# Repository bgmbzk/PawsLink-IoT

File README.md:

# 🐾 PawsLink IoT: The Elite Cat Gate Controller

Selam! Bu proje, evin asıl sahibi olan kedimin balkon kapısında mahsur kalma krizlerine (ve benim her seferinde bir "kapı görevlisi" edasıyla yerimden kalkmama) son vermek için geliştirildi. Başta küçük bir can sıkıntısı gibi görünse de, süreç içinde evrim geçirerek tam kapsamlı bir **Embedded System & IoT** projesine dönüştü.

## 📸 Tasarım Süreci ve Görseller

### 🎨 Şematik Tasarım
Projenin elektriksel bağlantıları ve ESP32 entegrasyonu:

---

### 🛣️ PCB Layout
Hassas sinyal yolları ve RF performansını korumak için tasarlanan Anten Keep-out bölgesi:

---

### 🧊 3D Modelleme
Üretim sonrası kartın fiziksel görünümü ve komponent yerleşimi:

## 🐱 Neden PawsLink?
Kedim, balkona çıkmak istediğinde kapının önünde kendine has bir frekansta seslenerek beni göreve çağırıyor. **PawsLink**, bu işitsel sinyalleri (miyavlamaları) algılayıp mekanik bir kolu tetikleyen, böylece kedime kendi özgürlüğünü sunan akıllı bir sistemdir.

## 🛠 Teknik Gelişim & Mühendislik Detayları
Proje başlangıçta **ATmega** tabanlıydı; ancak hem performansını artırmak hem de modern bağlantı özelliklerinden (Wi-Fi/Bluetooth) faydalanmak amacıyla mimariyi **ESP32**’ye taşıdım. Tasarımda dikkat ettiğim bazı kritik teknik noktalar:

* **RF Performansı (Anten Keep-out):** ESP32'nin üzerindeki PCB antenin verimli çalışması için, antenin altında kalan tüm katmanlarda bakır dökümü iptal edildi (No-copper zone).
* **Hassas PCB Layout:** USB-C güç girişi gibi yüksek yoğunluklu pinlerde kısa devre riskini önlemek için özel clearance (güvenlik mesafesi) ayarları yapıldı.
* **EMI ve Gürültü Yönetimi:** Güç hatları üzerine yerleştirilen decoupling kapasitörleri ile dijital gürültü minimize edildi, analog ses sensörünün daha kararlı çalışması sağlandı.
* **Hatasız Tasarım:** Endüstriyel standartlarda, **0 DRC Error** ve **0 Unconnected Items** ile üretime hazır hale getirildi.

 ---

# 🛠 Donanım Güncellemesi: V1.1 - Güç Optimizasyonu

Sistem kararlılığını ve motor performansını artırmak için yapılan iyileştirmeler:

* **Yol Kalınlaştırma (Power Tracks):** Motoru besleyen ana hatlar ve motor çıkış yolları **40 mil (~1.0 mm)** genişliğine çıkarıldı. Bu sayede motorun çektiği anlık akım, kartta ısınmaya veya voltaj düşümüne sebep olmadan güvenle iletilebiliyor.
* **Güç Otobanı:** Barrel Jack girişinden başlayarak Diyot, Kapasitörler ve Motor Sürücüye (DRV8833) giden hat "Güç Otobanı" mantığıyla optimize edildi. Bu güncelleme, motor zorlandığında bile ESP32'nin stabil çalışmasını (brown-out önleme) sağlar.
* **GND Plane:** Toprak hattı kesintisiz bakır döküm (GND Plane) olarak tasarlanarak hem parazitler engellendi hem de termal yönetim iyileştirildi.

---

## 📂 Dosya Yapısı
* `/Hardware`: KiCad şematik ve PCB layout dosyaları.
* `/Production`: Üretime hazır Gerber ve Drill dosyaları (PawsLink_Final_v1.zip).
* `/Firmware`: ESP32 için yazılmış IoT kontrol kodları.

---

### 🚀 Nasıl Çalışır?
1. PCB sipariş edilir ve bileşenler lehimlenir.
2. ESP32 yazılımı yüklenir.
3. Kedinin "miyav" frekansı kalibre edilir.
4. Koltuğa yaslanılır ve kedinin kendi kapısını açışı izlenir. ✨

---

## 🚀 Son Güncellemeler (Mayıs 2026)

Bu donanım revizyonu, güvenlik önlemlerine odaklanmakta ve sistemi akıllı yazılım entegrasyonuna hazırlamaktadır. Proje, kapı hareketi sırasında kedi güvenliğini sağlamak için proaktif önlemler içerecek şekilde geliştirilmiştir.

### Donanım v1.2 İyileştirmeleri
*   **Akıllı Engel Algılama**: HuskyLens entegrasyonu için özel bir 4-pinli konnektör (**J4**) eklendi. Bu sayede, mekanizma çalışmadan önce yapay zeka destekli algılama ile kedinin kapı eşiğinde olup olmadığı kontrol edilebilecektir.
*   **Görsel Durum LED'i**: Sistem durumunu ve olası engelleri gerçek zamanlı olarak bildirmek için yeni bir gösterge LED'i eklendi.
*   **Güç Kararlılığı**: ESP32 ve motor sürücüsünün yük altında kararlı çalışması için PCB yolları, net atamaları (USB-C pin eşleme düzeltmeleri dahil) ve bakır alanlar optimize edildi.
*   **Üretime Hazır Düzen**: Fiziksel PCB üretimine hazırlık amacıyla tasarım kuralı hataları (DRC) ve açıklık (clearance) ihlalleri giderildi.

### Güncel Proje Görselleri

#### Yeni Şematik Tasarımı

#### Yeni PCB Tasarımı

#### 3D Donanım Modeli

## 💻 Yazılım Özellikleri (Firmware)

Projenin yazılımı ESP32 üzerinde C++ (Arduino) kullanılarak geliştirilmiştir. Temel çalışma mantığı şu şekildedir:

* **Tetikleme:** LM358 amfi devresi üzerinden gelen analog ses verisiyle kedinin miyavlaması algılanır.
* **Güvenlik:** HuskyLens AI kamera, I2C üzerinden ESP32 ile haberleşerek kedinin kapı eşiğinde olup olmadığını denetler.
* **Akıllı Döngü:** Kapı sadece miyavlama duyulduğunda açılır ve kedi eşikten tamamen ayrıldığında (HuskyLens onayıyla) güvenli bir şekilde kapanır.
* **Enerji Tasarrufu:** DRV8833 motor sürücüsü, işlem yapılmadığı anlarda `SLEEP` moduna alınarak güç tüketimi minimize edilir.
---

*Not: Bu donanım versiyonu ile eşzamanlı geliştirilen ESP32 yazılımı güncellenmelere açıktır. *

**Not2:** Bu proje yapılırken hiçbir kedi mahsur bırakılmamıştır. Aksine, artık evin kapıları onun kontrolü altında! 🐈‍⬛🚀

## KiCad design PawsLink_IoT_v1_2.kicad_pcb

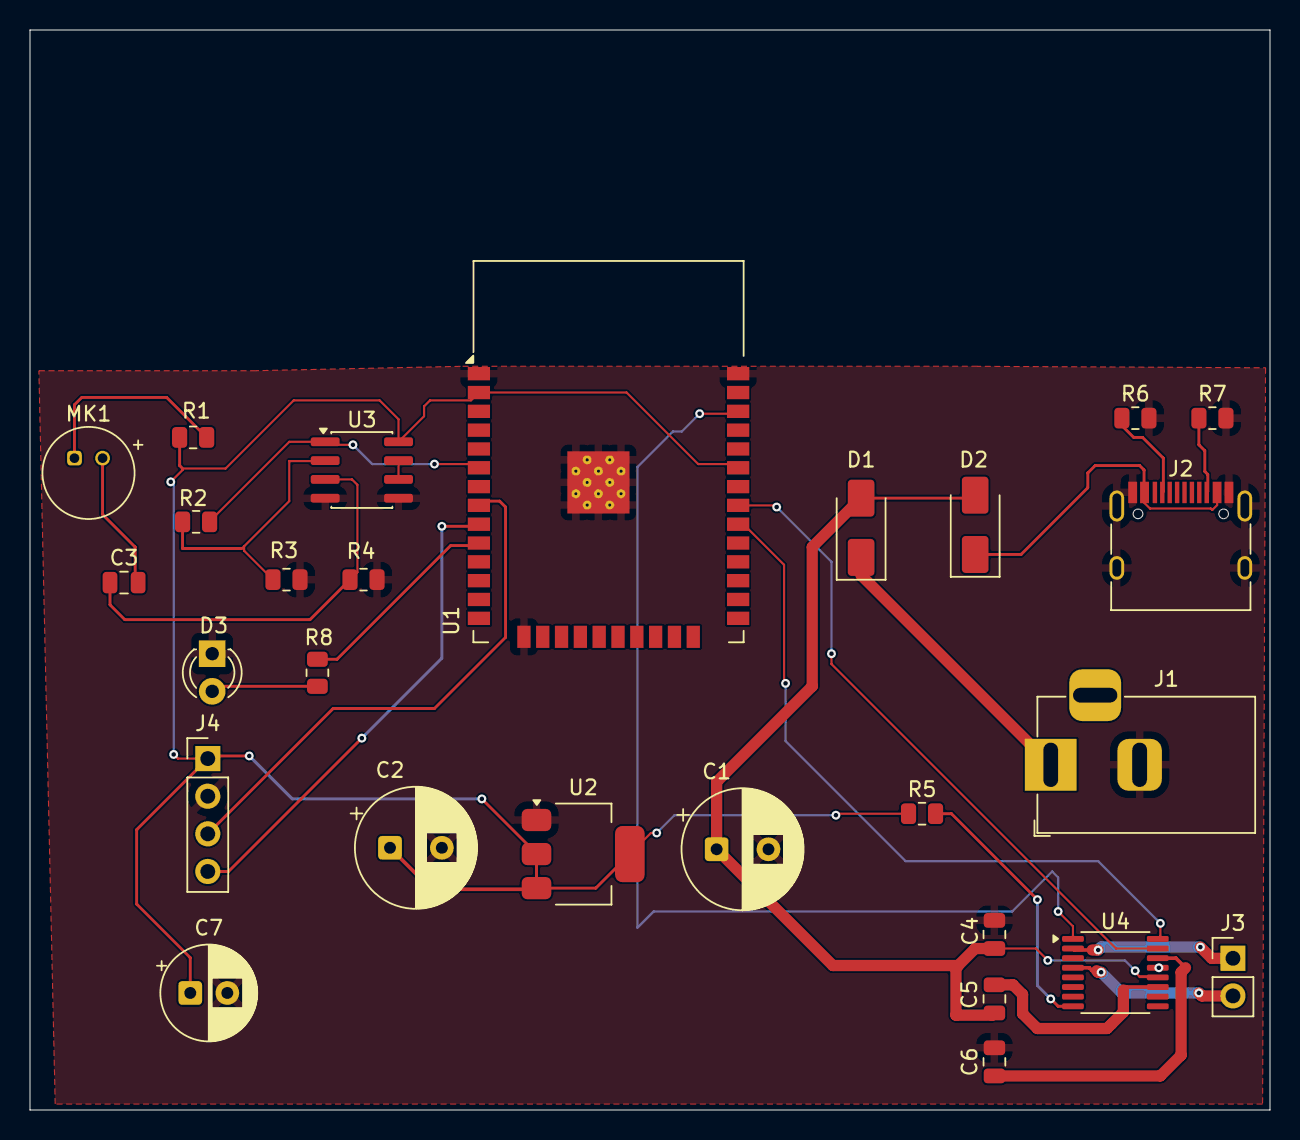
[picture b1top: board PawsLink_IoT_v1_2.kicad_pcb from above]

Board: 2 copper layers, 83.7 x 72.9 mm, 27 parts (0 on the bottom side), 25 nets.

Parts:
C1, C2: C_Polarized; CP_Radial_D8.0mm_P3.50mm
C3: 100nF; C_0805_2012Metric
C4: 100uF; C_0805_2012Metric
C5: 10nF; C_0805_2012Metric
C6: 2.2muF; C_0805_2012Metric
C7: 100uF; CP_Radial_D6.3mm_P2.50mm
D1, D2: SS34; D_SMA
D3: LED; LED_D3.0mm
J1: Barrel_Jack_MountingPin; BarrelJack_Horizontal
J2: USB_C_Receptacle_PowerOnly_6P; USB_C_Receptacle_HRO_TYPE-C-31-M-12
J3: Conn_01x02; PinHeader_1x02_P2.54mm_Vertical
J4: Conn_01x04; PinHeader_1x04_P2.54mm_Vertical
MK1: Microphone_Condenser; POM-2244P-C3310-2-R
R1: 2.2k; R_0805_2012Metric
R2: 100kΩ; R_0805_2012Metric
R3: 1kΩ; R_0805_2012Metric
R4: 1MΩ; R_0805_2012Metric
R5: 10kΩ; R_0805_2012Metric
R6, R7: 5.1kΩ; R_0805_2012Metric
R8: 220; R_0805_2012Metric
U1: ESP32-WROOM-32
U2: AMS1117CS-3.3; SOT-223-3_TabPin2
U3: LM358; SOIC-8_3.9x4.9mm_P1.27mm
U4: DRV8833PW; TSSOP-16_4.4x5mm_P0.65mm

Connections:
GND: C1.2, C2.2, C4.2, C6.2, C7.2, D3.1 (K), J1.2, J2.A1, J2.A12 (GND), J2.B1, J2.B12 (GND), J2.S1 (SHIELD), J4.2, R3.2, R4.2, R6.2, R7.2, U1.1 (GND), U1.15 (GND), U1.38 (GND), U1.39 (GND), U2.1 (GND), U3.4 (V-), U3.5 (+), U4.13 (GND)
unnamed: C1.1, C4.1, C5.2, D1.2 (A), D2.2 (A), U4.12 (VM)
unnamed: D1.1 (K), J1.1
unnamed: D2.1 (K), J2.A4, J2.A9 (VBUS), J2.B4, J2.B9 (VBUS)
unnamed: D3.2 (A), R8.2
unnamed: J2.A5 (CC1), R6.1
unnamed: J2.B5 (CC2), R7.1
unnamed: J3.1, U4.2 (AOUT1)
unnamed: J3.2, U4.4 (AOUT2)
unnamed: C2.1, C7.1, J4.1, R1.1, R5.1, U1.2 (VDD), U1.33 (IO21), U2.2 (VO), U2.3 (VO), U3.8 (V+)
unnamed: J4.3, U1.8 (IO32)
unnamed: J4.4, U1.9 (IO33)
unnamed: C3.2, MK1.2 (+)
unnamed: MK1.1 (-), R1.2
unnamed: U1.30 (IO18), U4.16 (AIN1)
unnamed: U1.31 (IO19), U4.15 (AIN2)
unnamed: U1.36 (IO22), U4.1 (~SLEEP)
unnamed: R8.1, U1.10 (IO25)
unnamed: R2.2, U1.6 (IO34), U3.1
unnamed: C3.1, R4.1, U3.3 (+)
unnamed: R2.1, R3.1, U3.2 (-)
unnamed: U3.6 (-), U3.7
unnamed: C5.1, U4.11 (VCP)
unnamed: C6.1, U4.14 (VINT)
unnamed: R5.2, U4.8 (~FAULT)

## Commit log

2026-04-29 Fix typo in README.md description
    Corrected a typo in the description of PawsLink.
2026-04-29 Add hardware update V1.1 for power optimization
    Refactor: Widen power traces to 40mils for increased current capacity and system stability
2026-05-06 v1.2 Update: STM32 Shift & PCB Design
    ESP32 Hardware Update: Refined the existing ESP32-based design for better stability and future firmware development.
    Safety Features: Added a dedicated LED and HuskyLens connector (J4) to detect if the cat is standing in the doorway, preventing accidental closure.
    PCB Refinement: Optimized power routing and component placement to ensure reliable sensor data for the upcoming coding phase.
    Ready for Firmware: Hardware is now fully prepared for the next step: writing the ESP32 logic for cat-detection and automated door control.
2026-05-06 Document hardware v1.2 updates and project visuals
    Added updates regarding hardware revisions and improvements for cat door safety and smart software integration.
2026-05-11 Create PawsLink_Main_v1.ino
    Add: Initial ESP32 firmware for cat detection and motor control
2026-05-11 Add Yazılım Özellikleri section to README
    Add: Initial ESP32 firmware for cat detection and motor control
2026-05-11 Revise note on ESP32 software updates
    Updated note regarding ESP32 software development readiness.
